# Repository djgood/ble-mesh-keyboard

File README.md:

# BLE Split Keyboard Project

## Project Structure

    ├── doc             # datasheets, app notes, references
    ├── firmware        # Zephyr project files (TODO)
    ├── hardware        # KiCAD project files 

## Block Diagram

View this project on [CADLAB.io](https://cadlab.io/project/22910).

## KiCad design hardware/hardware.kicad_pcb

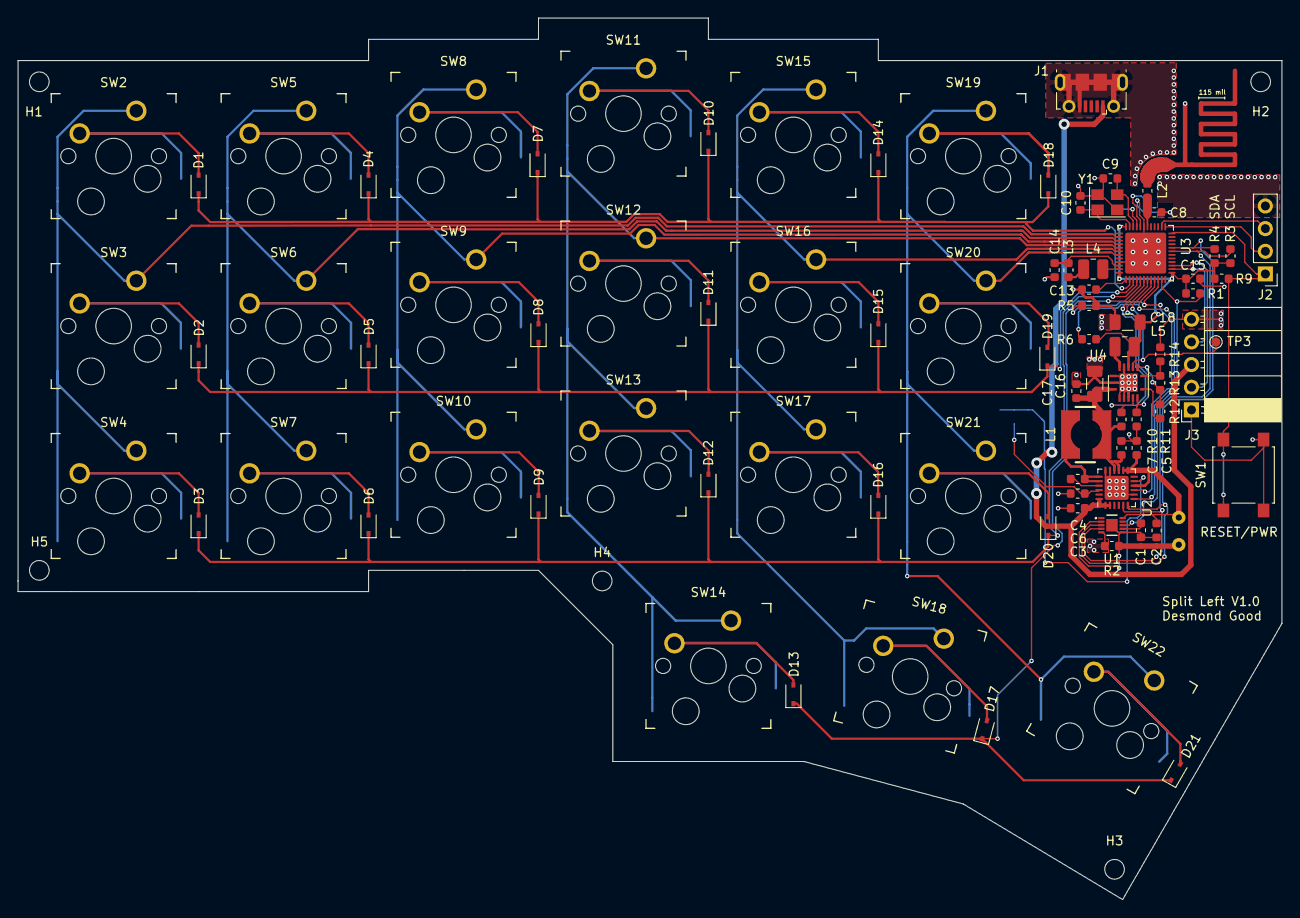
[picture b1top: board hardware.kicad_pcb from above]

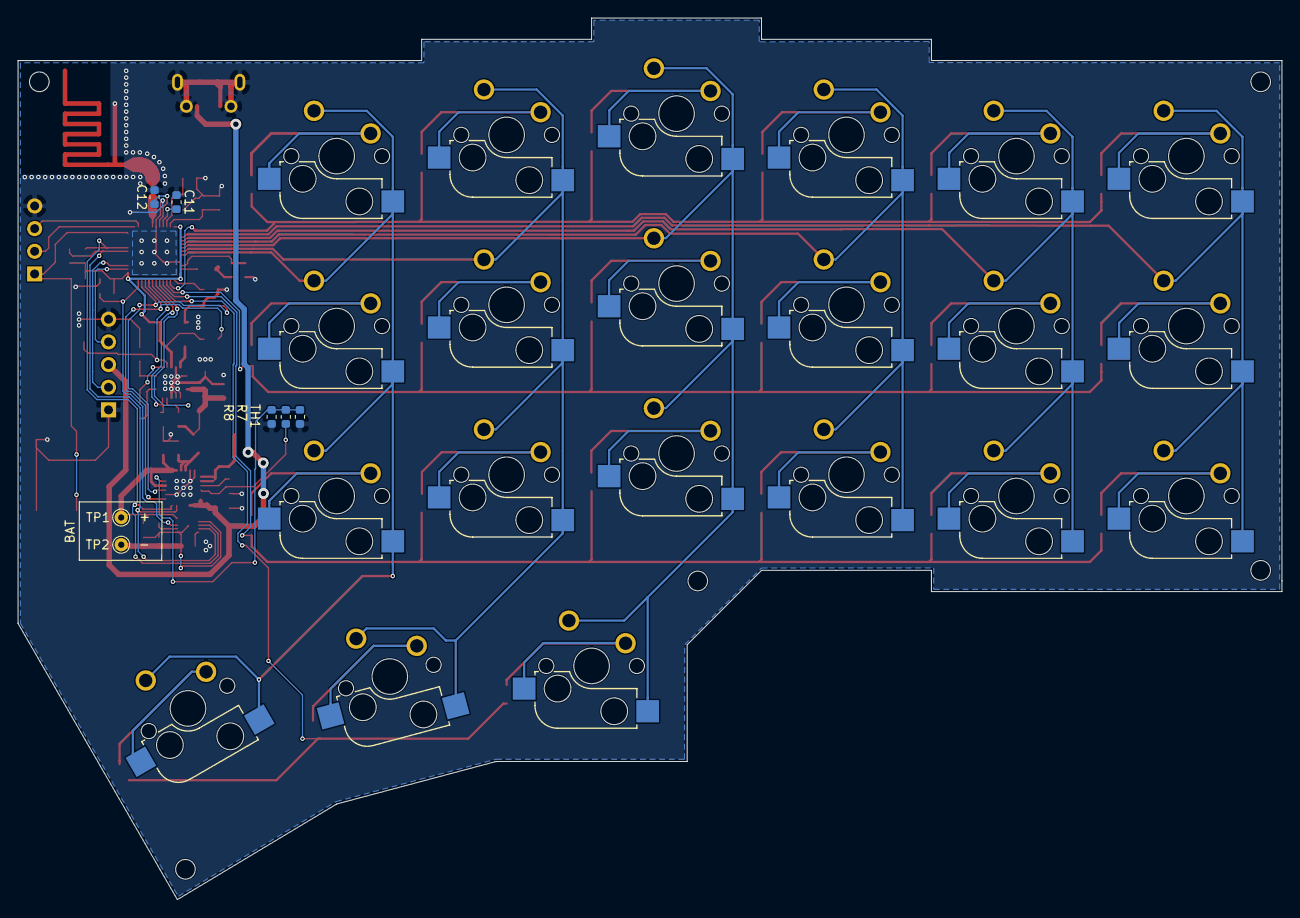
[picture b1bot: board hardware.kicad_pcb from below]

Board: 2 copper layers, 141.7 x 98.8 mm, 97 parts (7 on the bottom side), 68 nets.

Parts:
C1: 470nF; R_0603_1608Metric
C2, C13, C15, C17: 0.1uF; R_0603_1608Metric
C3, C14: 1uF; C_0603_1608Metric
C4: 47nF; C_0603_1608Metric
C5, C7: 10uF; C_0603_1608Metric
C6: 4.7uF; C_0603_1608Metric
C8: 0.8pF; C_0603_1608Metric
C9, C10: 12pF; C_0603_1608Metric
C11: 100pF; C_0603_1608Metric
C12: N.C.; R_0603_1608Metric
C16, C18: 22uF; R_1206_3216Metric
D1, D2, D3, D4, D5, D6, D7, D8, D9, D10, D11, D12, D13, D14, D15, D16, D17, D18, D19, D20, D21: 1N4148WSTR; D_SOD-323
H1, H2, H3, H4, H5: MountingHole; MountingHole_2.2mm_M2
J1: USB_B_Micro; USB_Micro-B_Molex-105017-0001
J2: Conn_01x04_Male; PinHeader_1x04_P2.54mm_Vertical
J3: Conn_01x05; PinSocket_1x05_P2.54mm_Horizontal
L1: 2.2 uH; WE-TPC4828
L2: 3.9nH; L_0603_1608Metric
L3: 15nH; L_0603_1608Metric
L4, L5: 10uH; L_1008_2520Metric
R1, R3, R4, R5, R6, R9, R10, R11: 10k; R_0603_1608Metric
R2: 10m; R_0603_1608Metric
R7: 3.65k; R_0603_1608Metric
R8: 14.3k; R_0603_1608Metric
R12: 7.87M; R_0603_1608Metric
R13: 715k; R_0603_1608Metric
R14: 4.53M; R_0603_1608Metric
SW1: SW_Push; SW_SPST_B3S-1000
SW2, SW3, SW4, SW5, SW6, SW7, SW8, SW9, SW10, SW11, SW12, SW13, SW14, SW15, SW16, SW17, SW18, SW19, SW20, SW21, SW22: MX Socket; Kailh_socket_MX_optional
TH1: NTC 10k; R_0603_1608Metric
TP1: BAT+; TestPoint_THTPad_D1.5mm_Drill0.7mm
TP2: BAT-; TestPoint_THTPad_D1.5mm_Drill0.7mm
TP3: TP_DCDC_OK; TestPoint_Pad_D1.0mm
U1: MAX17055ETB+T; TDFN-10-1EP_2.05mmx2.55mm_P0.4mm
U2: BQ25619RTWR; Texas_S-PWQFN-N24_EP2.7x2.7mm
U3: nRF52810-QFxx; QFN-48-1EP_6x6mm_P0.4mm_EP4.6x4.6mm
U4: TPS62736; Texas_S-PVQFN-N14
Y1: 32 MHz; Crystal_SMD_Abracon_ABM8G-4Pin_3.2x2.5mm

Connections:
+3V0: C15.1, C18.1, L5.2, R1.1, R3.1, R4.1, R6.1, R9.1, U3.13, U3.36, U3.48, U4.11
+BATT: C2.1, C5.2, TP1.1, U1.10, U2.10, U2.13, U2.14
-BATT: C1.2, C2.2, R2.1, TP2.1, U1.2, U1.6, U1.11
/Battery/Charging/CHARGER_~CE: R5.1, U2.9, U3.10
/Battery/Charging/CHARGER_~INT: R6.2, U2.7, U3.9
/Battery/Charging/GUAGE_~INT: R1.2, U1.8, U3.11
/Battery/Charging/REGN: C6.1, R7.1, U2.22
/Battery/Charging/SCL: R3.2, U1.4, U2.5, U3.19
/Battery/Charging/SDA: R4.2, U1.3, U2.6, U3.20
/Battery/Charging/VSYS: C7.2, C16.1, C17.1, L1.2, R10.1, U2.15, U2.16, U4.1
/Power/DCDC_EN1: R10.2, U3.6, U4.5
/Power/DCDC_EN2: R11.1, U3.7, U4.6
/Power/DCDC_OK: TP3.1, U3.8, U4.10
/nRF52810/ANT: C8.1, L2.2, U3.30
/nRF52810/Keyboard Matrix/COL0: SW2.1, SW3.1, SW4.1, U3.38
/nRF52810/Keyboard Matrix/COL1: SW5.1, SW6.1, SW7.1, U3.39
/nRF52810/Keyboard Matrix/COL2: SW8.1, SW9.1, SW10.1, U3.40
/nRF52810/Keyboard Matrix/COL3: SW11.1, SW12.1, SW13.1, SW14.1, U3.41
/nRF52810/Keyboard Matrix/COL4: SW15.1, SW16.1, SW17.1, SW18.1, U3.42
/nRF52810/Keyboard Matrix/COL5: SW19.1, SW20.1, SW21.1, SW22.1, U3.43
/nRF52810/Keyboard Matrix/ROW0: D1.1, D4.1, D7.1, D10.1, D14.1, D18.1, U3.2
/nRF52810/Keyboard Matrix/ROW1: D2.1, D5.1, D8.1, D11.1, D15.1, D19.1, U3.3
/nRF52810/Keyboard Matrix/ROW2: D3.1, D6.1, D9.1, D12.1, D16.1, D20.1, U3.4
/nRF52810/Keyboard Matrix/ROW3: D13.1, D17.1, D21.1, U3.5
/nRF52810/SWDCLK: J2.2, U3.25
/nRF52810/SWDIO: J2.3, U3.26
/nRF52810/UART_RX: J3.4, U3.14
/nRF52810/UART_TX: J3.2, U3.15
/nRF52810/~RESET: J2.1, R9.2, SW1.2, U3.24
GND: C3.1, C5.1, C6.2, C7.1, C8.2, C9.2, C10.2, C11.1, C12.2, C13.1, C14.2, C15.2, C16.2, C17.2, C18.2, J1.5, J1.6, J2.4, J3.1, J3.5, L2.1, R2.2, R5.2, R8.2, R11.2, R14.2, SW1.1, TH1.2, U1.5, U2.8, U2.17, U2.18, U2.25, U3.31, U3.45, U3.49, U4.2, U4.3, U4.4, U4.12, U4.14, U4.15, Y1.2, Y1.4
unnamed: C1.1, U1.7
unnamed: C4.1, L1.1, U2.19, U2.20
unnamed: C4.2, U2.21
unnamed: C9.1, U3.34, Y1.3
unnamed: C10.1, U3.35, Y1.1
unnamed: C11.2, U3.33
unnamed: C12.1, U3.32
unnamed: C13.2, U3.1
unnamed: C14.1, L3.1, U3.46
unnamed: D1.2, SW2.2
unnamed: D2.2, SW3.2
unnamed: D3.2, SW4.2
unnamed: D4.2, SW5.2
unnamed: D5.2, SW6.2
unnamed: D6.2, SW7.2
unnamed: D7.2, SW8.2
unnamed: D8.2, SW9.2
unnamed: D9.2, SW10.2
unnamed: D10.2, SW11.2
unnamed: D11.2, SW12.2
unnamed: D12.2, SW13.2
unnamed: D13.2, SW14.2
unnamed: D14.2, SW15.2
unnamed: D15.2, SW16.2
unnamed: D16.2, SW17.2
unnamed: D17.2, SW18.2
unnamed: D18.2, SW19.2
unnamed: D19.2, SW20.2
unnamed: D20.2, SW21.2
unnamed: D21.2, SW22.2
unnamed: L3.2, L4.1
unnamed: L4.2, U3.47
unnamed: L5.1, U4.13
unnamed: R7.2, R8.1, TH1.1, U2.11
unnamed: R12.1, U4.7
unnamed: R12.2, R13.1, U4.9
unnamed: R13.2, R14.1, U4.8
VBUS: C3.2, J1.1, J3.3, U2.1, U2.2, U2.24

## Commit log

2020-05-14 Initial prototype of keyboard
2020-05-14 Add repository configuration
2020-05-14 Add README.md
2020-05-14 Cleanup
2020-05-14 Remove *.sch-bak and *.kicad_pcb-bak files
2020-05-14 Backlink to CADLAB.io has been added.
2020-05-14 README.md: Update formatting
2020-05-17 Update the part number for R13
    The part number was specified as `603-RC0603FR-071KL` but should have
    been `RC0603FR-07715KL`. The part number in the schematic has been
    updated to reflect this.
2020-05-18 Invert pull-up/down supply for R10, R11
    The voltage for these resistors was wrong, so the 3V buck was configured
    to be in ship mode by default.
    The 3V buck will now start in enable mode with the following
    configuration:
    - R10 (EN2) = 1
    - R11 (EN1) = 0
2020-05-25 Add PCB and block diagram to README.md
2020-05-26 Make block diagram more pretty

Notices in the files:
parts and their libraries:
Copyright 2016 Accelerated Designs. All rights reserved.
